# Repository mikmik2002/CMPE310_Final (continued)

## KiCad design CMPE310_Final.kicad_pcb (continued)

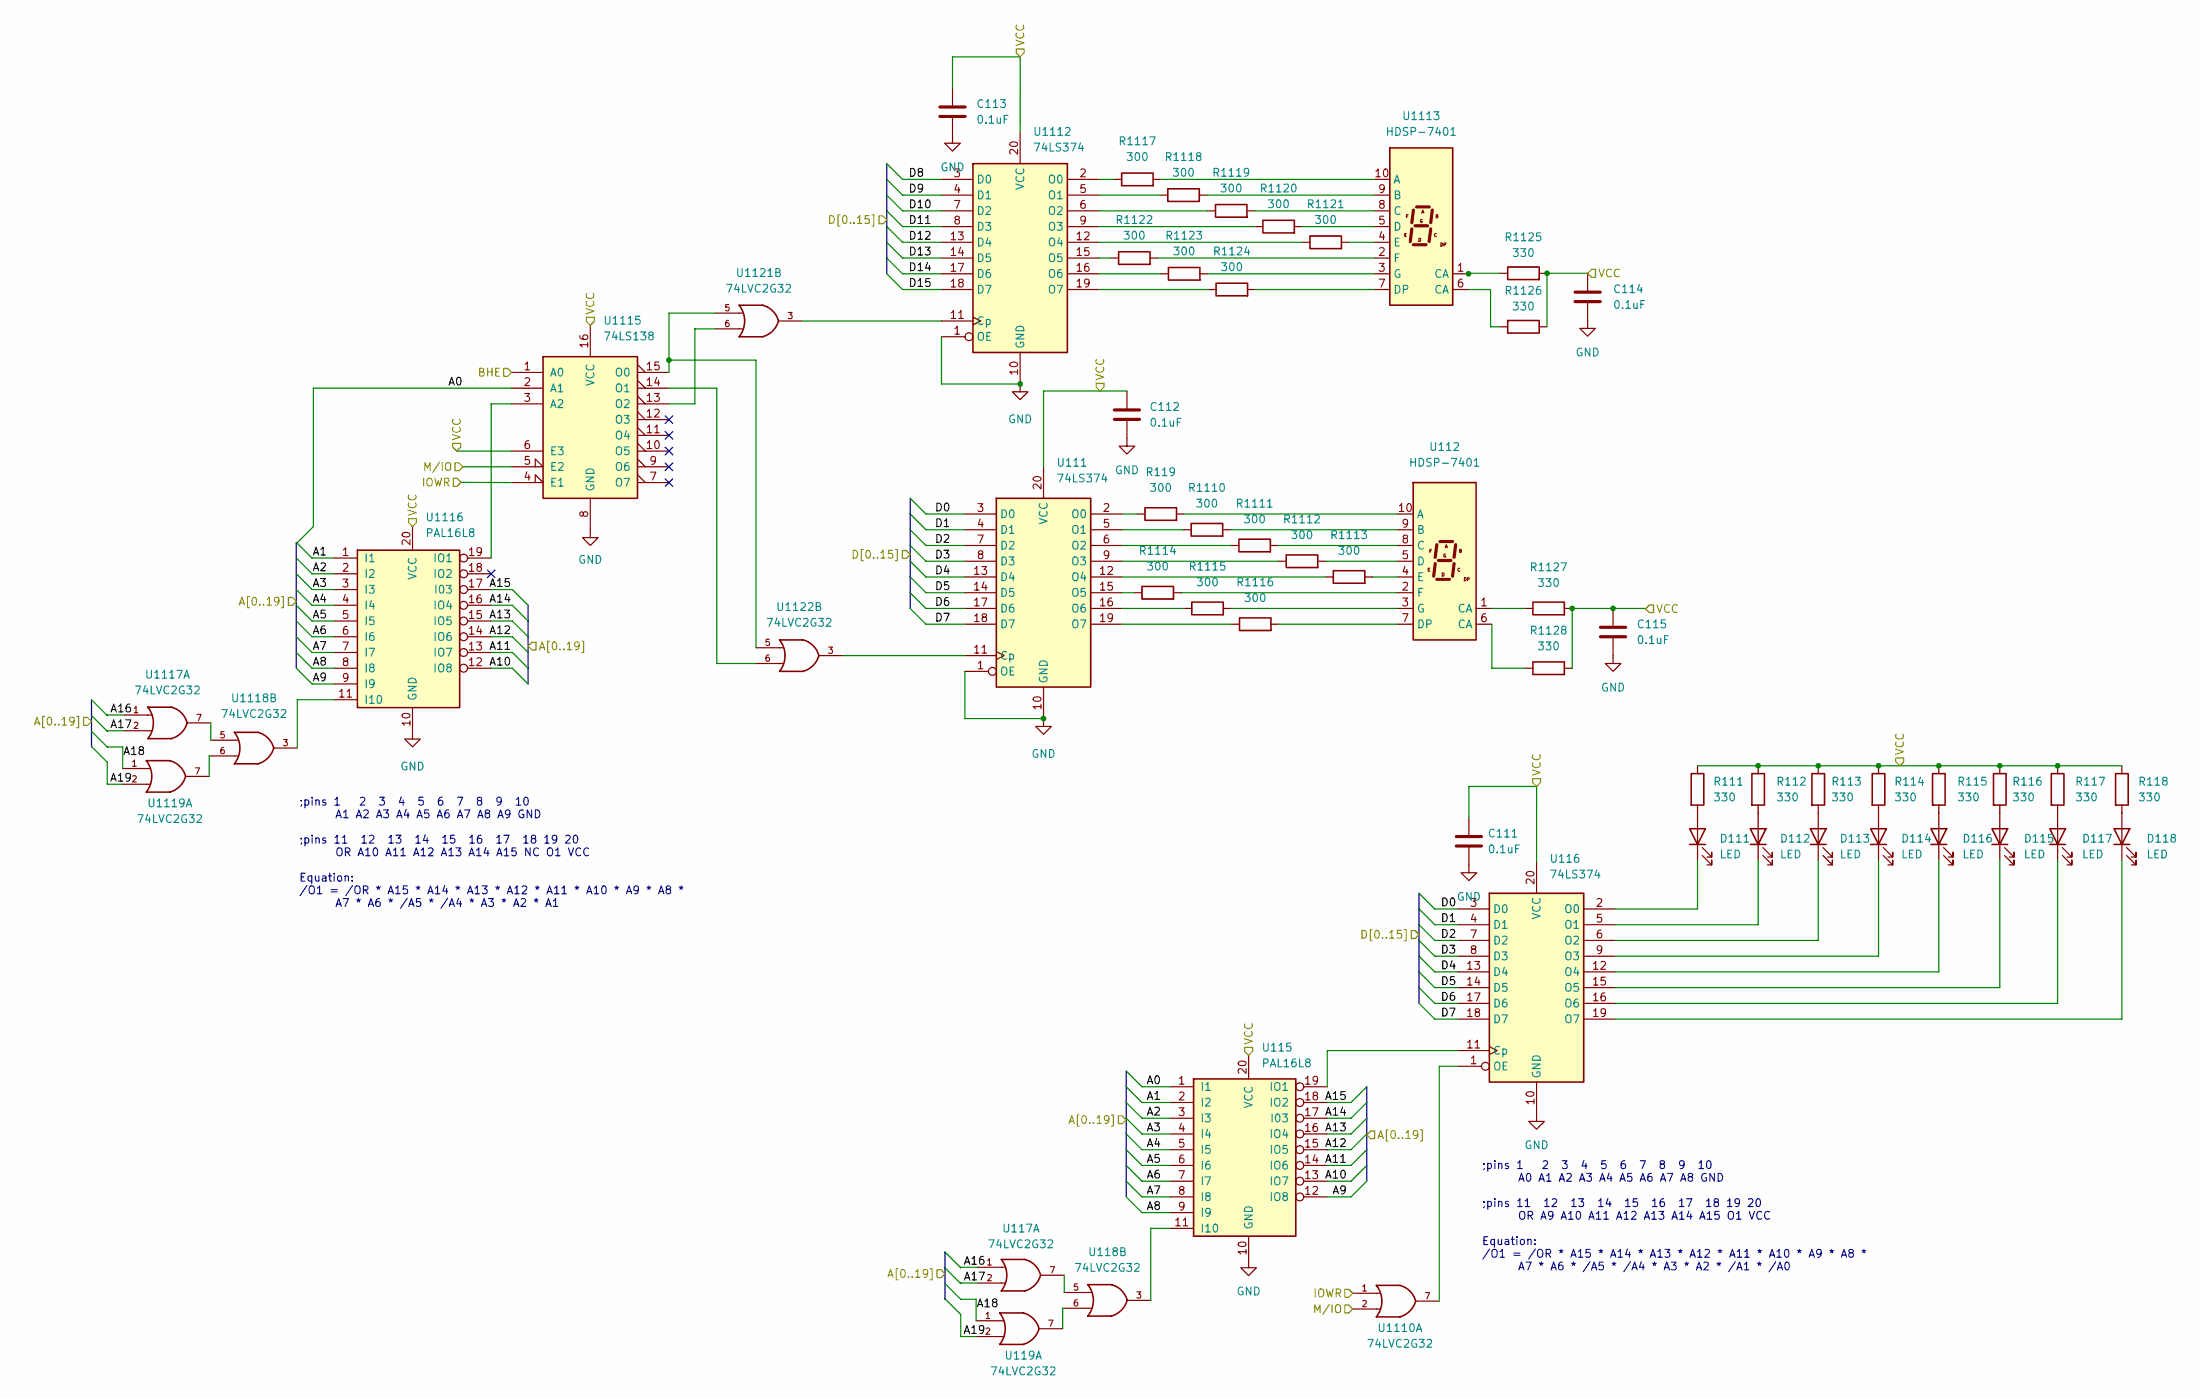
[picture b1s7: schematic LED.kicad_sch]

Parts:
C111, C112, C113, C114, C115: 0.1uF; C_Axial_L3.8mm_D2.6mm_P7.50mm_Horizontal
D111, D112, D113, D114, D115, D116, D117, D118: LED; LED_D1.8mm_W1.8mm_H2.4mm_Horizontal_O1.27mm_Z1.6mm
R111, R112, R113, R114, R115, R116, R117, R118, R1125, R1126, R1127, R1128: 330; R_Axial_DIN0204_L3.6mm_D1.6mm_P1.90mm_Vertical
R119, R1110, R1111, R1112, R1113, R1114, R1115, R1116, R1117, R1118, R1119, R1120, R1121, R1122, R1123, R1124: 300; R_Axial_DIN0204_L3.6mm_D1.6mm_P1.90mm_Vertical
U111, U116, U1112: 74LS374; DIP-20_W7.62mm
U112, U1113: HDSP-7401
U115, U1116: PAL16L8; DIP-20_W7.62mm
U117, U118, U119, U1110, U1117, U1118, U1119, U1121, U1122: 74LVC2G32
U1115: 74LS138; DIP-16_W7.62mm

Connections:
A0: U115.1 (I1), U1115.2 (A1); also elsewhere on the board
A1: U115.2 (I2), U1116.1 (I1); also elsewhere on the board
A2: U115.3 (I3), U1116.2 (I2); also elsewhere on the board
A3: U115.4 (I4), U1116.3 (I3); also elsewhere on the board
A4: U115.5 (I5), U1116.4 (I4); also elsewhere on the board
A5: U115.6 (I6), U1116.5 (I5); also elsewhere on the board
A6: U115.7 (I7), U1116.6 (I6); also elsewhere on the board
A7: U115.8 (I8), U1116.7 (I7); also elsewhere on the board
A8: U115.9 (I9), U1116.8 (I8); also elsewhere on the board
A9: U115.12 (IO8), U1116.9 (I9); also elsewhere on the board
A10: U115.13 (IO7), U1116.12 (IO8); also elsewhere on the board
A11: U115.14 (IO6), U1116.13 (IO7); also elsewhere on the board
A12: U115.15 (IO5), U1116.14 (IO6); also elsewhere on the board
A13: U115.16 (IO4), U1116.15 (IO5); also elsewhere on the board
A14: U115.17 (I03), U1116.16 (IO4); also elsewhere on the board
A15: U115.18 (IO2), U1116.17 (I03); also elsewhere on the board
A16: U117.1, U1117.1; also elsewhere on the board
A17: U117.2, U1117.2; also elsewhere on the board
A18: U119.1, U1119.1; also elsewhere on the board
A19: U119.2, U1119.2; also elsewhere on the board
BHE: U1115.1 (A0); also elsewhere on the board
D0: U111.3 (D0), U116.3 (D0); also elsewhere on the board
D1: U111.4 (D1), U116.4 (D1); also elsewhere on the board
D2: U111.7 (D2), U116.7 (D2); also elsewhere on the board
D3: U111.8 (D3), U116.8 (D3); also elsewhere on the board
D4: U111.13 (D4), U116.13 (D4); also elsewhere on the board
D5: U111.14 (D5), U116.14 (D5); also elsewhere on the board
D6: U111.17 (D6), U116.17 (D6); also elsewhere on the board
D7: U111.18 (D7), U116.18 (D7); also elsewhere on the board
D8: U1112.3 (D0); also elsewhere on the board
D9: U1112.4 (D1); also elsewhere on the board
D10: U1112.7 (D2); also elsewhere on the board
D11: U1112.8 (D3); also elsewhere on the board
D12: U1112.13 (D4); also elsewhere on the board
D13: U1112.14 (D5); also elsewhere on the board
D14: U1112.17 (D6); also elsewhere on the board
D15: U1112.18 (D7); also elsewhere on the board
GND: C111.2, C112.2, C113.2, C114.2, C115.2, U111.1 (OE), U111.10 (GND), U115.10 (GND), U116.10 (GND), U117.4 (GND), U118.4 (GND), U119.4 (GND), U1110.4 (GND), U1112.1 (OE), U1112.10 (GND), U1115.8 (GND), U1116.10 (GND), U1117.4 (GND), U1118.4 (GND), U1119.4 (GND), U1121.4 (GND), U1122.4 (GND); also elsewhere on the board
M/IO: U1110.2, U1115.5 (E2); also elsewhere on the board
unnamed: D111.1 (K), U116.2 (O0)
unnamed: D111.2 (A), R111.2
unnamed: D112.1 (K), U116.5 (O1)
unnamed: D112.2 (A), R112.2
unnamed: D113.1 (K), U116.6 (O2)
unnamed: D113.2 (A), R113.2
unnamed: D114.1 (K), U116.9 (O3)
unnamed: D114.2 (A), R114.2
unnamed: D115.1 (K), U116.15 (O5)
unnamed: D115.2 (A), R116.2
unnamed: D116.1 (K), U116.12 (O4)
unnamed: D116.2 (A), R115.2
unnamed: D117.1 (K), U116.16 (O6)
unnamed: D117.2 (A), R117.2
unnamed: D118.1 (K), U116.19 (O7)
unnamed: D118.2 (A), R118.2
unnamed: R119.1, U111.2 (O0)
unnamed: R119.2, U112.10 (A)
unnamed: R1110.1, U111.5 (O1)
unnamed: R1110.2, U112.9 (B)
unnamed: R1111.1, U111.6 (O2)
unnamed: R1111.2, U112.8 (C)
unnamed: R1112.1, U111.9 (O3)
unnamed: R1112.2, U112.5 (D)
unnamed: R1113.1, U111.12 (O4)
unnamed: R1113.2, U112.4 (E)
unnamed: R1114.1, U111.15 (O5)
unnamed: R1114.2, U112.2 (F)
unnamed: R1115.1, U111.16 (O6)
unnamed: R1115.2, U112.3 (G)
unnamed: R1116.1, U111.19 (O7)
unnamed: R1116.2, U112.7 (DP)
unnamed: R1117.1, U1112.2 (O0)
unnamed: R1117.2, U1113.10 (A)
unnamed: R1118.1, U1112.5 (O1)
unnamed: R1118.2, U1113.9 (B)
unnamed: R1119.1, U1112.6 (O2)
unnamed: R1119.2, U1113.8 (C)
unnamed: R1120.1, U1112.9 (O3)
unnamed: R1120.2, U1113.5 (D)
unnamed: R1121.1, U1112.12 (O4)
unnamed: R1121.2, U1113.4 (E)
unnamed: R1122.1, U1112.15 (O5)
unnamed: R1122.2, U1113.2 (F)
unnamed: R1123.1, U1112.16 (O6)
unnamed: R1123.2, U1113.3 (G)
unnamed: R1124.1, U1112.19 (O7)
unnamed: R1124.2, U1113.7 (DP)
unnamed: R1125.1, U1113.1 (CA)
unnamed: R1126.2, U1113.6 (CA)
unnamed: R1127.1, U112.1 (CA)
unnamed: R1128.1, U112.6 (CA)
unnamed: U111.11 (Cp), U1122.3
unnamed: U115.11 (I10), U118.3
unnamed: U115.19 (IO1), U116.11 (Cp)
unnamed: U117.7, U118.5
unnamed: U118.6, U119.7
unnamed: U116.1 (OE), U1110.7
unnamed: U1112.11 (Cp), U1121.3
unnamed: U1115.3 (A2), U1116.19 (IO1)
unnamed: U1115.13 (O2), U1121.6
unnamed: U1115.14 (O1), U1122.6
unnamed: U1115.15 (O0), U1121.5, U1122.5
unnamed: U1116.11 (I10), U1118.3
unnamed: U1117.7, U1118.5
unnamed: U1118.6, U1119.7
VCC: C111.1, C112.1, C113.1, C114.1, C115.1, R111.1, R112.1, R113.1, R114.1, R115.1, R116.1, R117.1, R118.1, R1125.2, R1126.1, R1127.2, R1128.2, U111.20 (VCC), U115.20 (VCC), U116.20 (VCC), U117.8 (VCC), U118.8 (VCC), U119.8 (VCC), U1110.8 (VCC), U1112.20 (VCC), U1115.6 (E3), U1115.16 (VCC), U1116.20 (VCC), U1117.8 (VCC), U1118.8 (VCC), U1119.8 (VCC), U1121.8 (VCC), U1122.8 (VCC); also elsewhere on the board
WR: U1110.1, U1115.4 (E1); also elsewhere on the board

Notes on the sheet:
;pins 1 2 3 4 5 6 7 8 9 10 A0 A1 A2 A3 A4 A5 A6 A7 A8 GND ;pins 11 12 13 14 15 16 17 18 19 20 OR A9 A10 A11 A12 A13 A14 A15 O1 VCC Equation: /O1 = /OR * A15 * A14 * A13 * A12 * A11 * A10 * A9 * A8 * A7 * A6 * /A5 * /A4 * A3 * A2 * /A1 * /A0
;pins 1 2 3 4 5 6 7 8 9 10 A1 A2 A3 A4 A5 A6 A7 A8 A9 GND ;pins 11 12 13 14 15 16 17 18 19 20 OR A10 A11 A12 A13 A14 A15 NC O1 VCC Equation: /O1 = /OR * A15 * A14 * A13 * A12 * A11 * A10 * A9 * A8 * A7 * A6 * /A5 * /A4 * A3 * A2 * A1

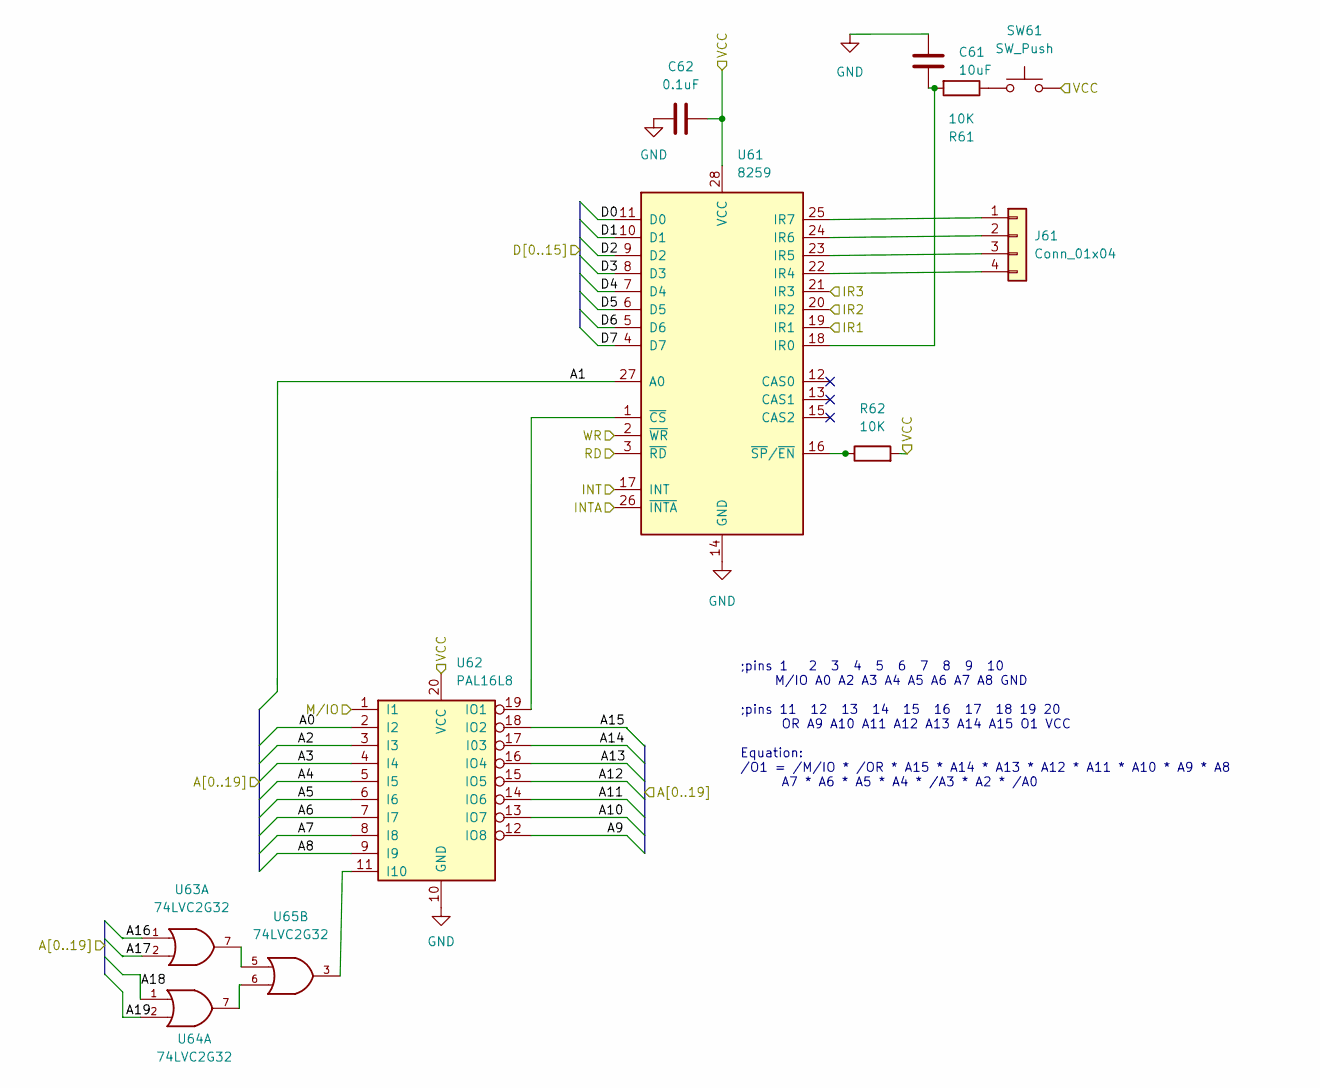
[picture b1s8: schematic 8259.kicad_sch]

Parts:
C61: 10uF; C_Axial_L3.8mm_D2.6mm_P7.50mm_Horizontal
C62: 0.1uF; C_Axial_L3.8mm_D2.6mm_P7.50mm_Horizontal
J61: Conn_01x04; PinHeader_1x04_P1.00mm_Vertical
R61, R62: 10K; R_Axial_DIN0204_L3.6mm_D1.6mm_P1.90mm_Vertical
SW61: SW_Push; SW_Tactile_Straight_KSA0Axx1LFTR
U61: 8259; DIP-28_W15.24mm
U62: PAL16L8; DIP-20_W7.62mm
U63, U64, U65: 74LVC2G32

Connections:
/8259 Bullet 6/IR2: U61.20 (IR2); also elsewhere on the board
A0: U62.2 (I2); also elsewhere on the board
A1: U61.27 (A0); also elsewhere on the board
A2: U62.3 (I3); also elsewhere on the board
A3: U62.4 (I4); also elsewhere on the board
A4: U62.5 (I5); also elsewhere on the board
A5: U62.6 (I6); also elsewhere on the board
A6: U62.7 (I7); also elsewhere on the board
A7: U62.8 (I8); also elsewhere on the board
A8: U62.9 (I9); also elsewhere on the board
A9: U62.12 (IO8); also elsewhere on the board
A10: U62.13 (IO7); also elsewhere on the board
A11: U62.14 (IO6); also elsewhere on the board
A12: U62.15 (IO5); also elsewhere on the board
A13: U62.16 (IO4); also elsewhere on the board
A14: U62.17 (I03); also elsewhere on the board
A15: U62.18 (IO2); also elsewhere on the board
A16: U63.1; also elsewhere on the board
A17: U63.2; also elsewhere on the board
A18: U64.1; also elsewhere on the board
A19: U64.2; also elsewhere on the board
D0: U61.11 (D0); also elsewhere on the board
D1: U61.10 (D1); also elsewhere on the board
D2: U61.9 (D2); also elsewhere on the board
D3: U61.8 (D3); also elsewhere on the board
D4: U61.7 (D4); also elsewhere on the board
D5: U61.6 (D5); also elsewhere on the board
D6: U61.5 (D6); also elsewhere on the board
D7: U61.4 (D7); also elsewhere on the board
GND: C61.2, C62.1, U61.14 (GND), U62.10 (GND), U63.4 (GND), U64.4 (GND), U65.4 (GND); also elsewhere on the board
INTA: U61.26 (~INTA); also elsewhere on the board
INTR: U61.17 (INT); also elsewhere on the board
IR1: U61.19 (IR1); also elsewhere on the board
IR3: U61.21 (IR3); also elsewhere on the board
M/IO: U62.1 (I1); also elsewhere on the board
unnamed: C61.1, R61.2, U61.18 (IR0)
unnamed: J61.1, U61.25 (IR7)
unnamed: J61.2, U61.24 (IR6)
unnamed: J61.3, U61.23 (IR5)
unnamed: J61.4, U61.22 (IR4)
unnamed: R61.1, SW61.1
unnamed: R62.1, U61.16 (~SP/~EN)
unnamed: U61.1 (~CS), U62.19 (IO1)
unnamed: U62.11 (I10), U65.3
unnamed: U63.7, U65.5
unnamed: U64.7, U65.6
RD: U61.3 (~RD); also elsewhere on the board
VCC: C62.2, R62.2, SW61.2, U61.28 (VCC), U62.20 (VCC), U63.8 (VCC), U64.8 (VCC), U65.8 (VCC); also elsewhere on the board
WR: U61.2 (~WR); also elsewhere on the board

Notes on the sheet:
;pins 1 2 3 4 5 6 7 8 9 10 M/IO A0 A2 A3 A4 A5 A6 A7 A8 GND ;pins 11 12 13 14 15 16 17 18 19 20 OR A9 A10 A11 A12 A13 A14 A15 O1 VCC Equation: /O1 = /M/IO * /OR * A15 * A14 * A13 * A12 * A11 * A10 * A9 * A8 A7 * A6 * A5 * A4 * /A3 * A2 * /A0

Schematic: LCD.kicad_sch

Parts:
DS101: LCD4x20; Mouser Part Number 763-0420AZFLYBW33V3
U102: PAL16L8; DIP-20_W7.62mm
U103, U104, U105: 74LVC2G32

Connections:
/LCD Bullet 10/CS: DS101.6 (E), U102.19 (IO1)
A0: U102.1 (I1); also elsewhere on the board
A1: DS101.4 (RS); also elsewhere on the board
A2: U102.2 (I2); also elsewhere on the board
A3: U102.3 (I3); also elsewhere on the board
A4: U102.4 (I4); also elsewhere on the board
A5: U102.5 (I5); also elsewhere on the board
A6: U102.6 (I6); also elsewhere on the board
A7: U102.7 (I7); also elsewhere on the board
A8: U102.8 (I8); also elsewhere on the board
A9: U102.9 (I9); also elsewhere on the board
A10: U102.12 (IO8); also elsewhere on the board
A11: U102.13 (IO7); also elsewhere on the board
A12: U102.14 (IO6); also elsewhere on the board
A13: U102.15 (IO5); also elsewhere on the board
A14: U102.16 (IO4); also elsewhere on the board
A15: U102.17 (I03); also elsewhere on the board
A16: U103.1; also elsewhere on the board
A17: U103.2; also elsewhere on the board
A18: U104.1; also elsewhere on the board
A19: U104.2; also elsewhere on the board
D0: DS101.7 (DB0); also elsewhere on the board
D1: DS101.8 (DB1); also elsewhere on the board
D2: DS101.9 (DB2); also elsewhere on the board
D3: DS101.10 (DB3); also elsewhere on the board
D4: DS101.14 (DB7); also elsewhere on the board
D5: DS101.13 (DB6); also elsewhere on the board
D6: DS101.12 (DB5); also elsewhere on the board
D7: DS101.11 (DB4); also elsewhere on the board
GND: DS101.2 (VDD), DS101.16 (LED-), U102.10 (GND), U103.4 (GND), U104.4 (GND), U105.4 (GND); also elsewhere on the board
unnamed: U102.11 (I10), U105.3
unnamed: U103.7, U105.5
unnamed: U104.7, U105.6
VCC: DS101.1 (VSS), DS101.3 (V0), DS101.15 (LED+), U102.20 (VCC), U103.8 (VCC), U104.8 (VCC), U105.8 (VCC); also elsewhere on the board
WR: DS101.5 (R/W); also elsewhere on the board

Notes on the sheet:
;pins 1 2 3 4 5 6 7 8 9 10 A0 A2 A3 A4 A5 A6 A7 A8 A9 GND ;pins 11 12 13 14 15 16 17 18 19 20 OR A10 A11 A12 A13 A14 A15 NC O1 VCC Equation: /O1 = /OR * A15 * A14 * A13 * A12 * A11 * A10 * A9 * A8 * A7 * A6 * /A5 * A4 * /A3 * A2 * /A0

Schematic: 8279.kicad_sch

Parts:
C81: 0.1uF; C_Axial_L3.8mm_D2.6mm_P7.50mm_Horizontal
SW81, SW82, SW83, SW84, SW85, SW86, SW87, SW88, SW89, SW810, SW811, SW812, SW813, SW814, SW815, SW816, SW817, SW818, SW819, SW820, SW821, SW822: SW_Push; SW_Tactile_Straight_KSA0Axx1LFTR
U81: pkd8279
U82: PAL16L8; DIP-20_W7.62mm
U83, U84, U85: 74LVC2G32
U86: 74LS138; DIP-16_W7.62mm

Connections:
/8086 Bullet One/Reset: U81.9 (RESET); also elsewhere on the board
/8259 Bullet 6/IR2: U81.4 (IRQ); also elsewhere on the board
/8279 Bullet 8/RL0: SW83.1, SW84.1, SW85.1, SW86.1, SW87.1, U81.38 (RL0)
/8279 Bullet 8/RL1: SW88.1, SW89.1, SW810.1, SW811.1, SW812.1, U81.39 (RL1)
/8279 Bullet 8/RL2: SW813.1, SW814.1, SW815.1, SW816.1, SW817.1, U81.1 (RL2)
/8279 Bullet 8/RL3: SW818.1, SW819.1, SW820.1, SW821.1, SW822.1, U81.2 (RL3)
/8279 Bullet 8/SL0: U81.32 (SL0), U86.1 (A0)
/8279 Bullet 8/SL1: U81.33 (SL1), U86.2 (A1)
/8279 Bullet 8/SL2: U81.34 (SL2), U86.3 (A2)
A0: U82.2 (I2); also elsewhere on the board
A1: U81.21 (A0); also elsewhere on the board
A2: U82.3 (I3); also elsewhere on the board
A3: U82.4 (I4); also elsewhere on the board
A4: U82.5 (I5); also elsewhere on the board
A5: U82.6 (I6); also elsewhere on the board
A6: U82.7 (I7); also elsewhere on the board
A7: U82.8 (I8); also elsewhere on the board
A8: U82.9 (I9); also elsewhere on the board
A9: U82.12 (IO8); also elsewhere on the board
A10: U82.13 (IO7); also elsewhere on the board
A11: U82.14 (IO6); also elsewhere on the board
A12: U82.15 (IO5); also elsewhere on the board
A13: U82.16 (IO4); also elsewhere on the board
A14: U82.17 (I03); also elsewhere on the board
A15: U82.18 (IO2); also elsewhere on the board
A16: U83.1; also elsewhere on the board
A17: U83.2; also elsewhere on the board
A18: U84.1; also elsewhere on the board
A19: U84.2; also elsewhere on the board
D0: U81.12 (DB0); also elsewhere on the board
D1: U81.13 (DB1); also elsewhere on the board
D2: U81.14 (DB2); also elsewhere on the board
D3: U81.15 (DB3); also elsewhere on the board
D4: U81.16 (DB4); also elsewhere on the board
D5: U81.17 (DB5); also elsewhere on the board
D6: U81.18 (DB6); also elsewhere on the board
D7: U81.19 (DB7); also elsewhere on the board
GND: C81.1, SW81.2, SW82.2, U81.20 (VSS), U82.10 (GND), U83.4 (GND), U84.4 (GND), U85.4 (GND), U86.4 (E1), U86.5 (E2), U86.8 (GND); also elsewhere on the board
M/IO: U82.1 (I1); also elsewhere on the board
unnamed: SW81.1, U81.37 (CNTL/STB)
unnamed: SW82.1, U81.36 (SHIFT)
unnamed: SW85.2, SW810.2, SW815.2, SW820.2, U86.13 (O2)
unnamed: SW86.2, SW811.2, SW816.2, SW821.2, U86.12 (O3)
unnamed: SW87.2, SW812.2, SW817.2, SW822.2, U86.11 (O4)
unnamed: SW83.2, SW88.2, SW813.2, SW818.2, U86.15 (O0)
unnamed: SW84.2, SW89.2, SW814.2, SW819.2, U86.14 (O1)
unnamed: U81.22 (~CS), U82.19 (IO1)
unnamed: U82.11 (I10), U85.3
unnamed: U83.7, U85.5
unnamed: U84.7, U85.6
PCLK: U81.3 (CLK); also elsewhere on the board
RD: U81.10 (~RD); also elsewhere on the board
VCC: C81.2, U81.5 (RL4), U81.6 (RL5), U81.7 (RL6), U81.8 (RL7), U81.40 (VCC), U82.20 (VCC), U83.8 (VCC), U84.8 (VCC), U85.8 (VCC), U86.6 (E3), U86.16 (VCC); also elsewhere on the board
WR: U81.11 (~WR); also elsewhere on the board

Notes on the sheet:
;pins 1 2 3 4 5 6 7 8 9 10 M/IO A0 A2 A3 A4 A5 A6 A7 A8 GND ;pins 11 12 13 14 15 16 17 18 19 20 OR A9 A10 A11 A12 A13 A14 A15 O1 VCC Equation: /O1 = /M/IO * /OR * A15 * A14 * A13 * A12 * A11 * A10 * A9 * A8 A7 * A6 * A5 * A4 * /A3 * /A2 * /A0

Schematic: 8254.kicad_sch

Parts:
C71: 0.1uF; C_Axial_L3.8mm_D2.6mm_P7.50mm_Horizontal
J71, J73: Conn_01x03; PinHeader_1x03_P1.00mm_Vertical
J72: Conn_01x02; PinHeader_1x02_P1.00mm_Vertical
U71: 8254; DIP-24_W15.24mm
U72: PAL16L8; DIP-20_W7.62mm
U73: 74LVC1G332

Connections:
A0: U72.2 (I2); also elsewhere on the board
A1: U71.19 (A0); also elsewhere on the board
A2: U71.20 (A1); also elsewhere on the board
A3: U72.3 (I3); also elsewhere on the board
A4: U72.4 (I4); also elsewhere on the board
A5: U72.5 (I5); also elsewhere on the board
A6: U72.6 (I6); also elsewhere on the board
A7: U72.7 (I7); also elsewhere on the board
A8: U72.8 (I8); also elsewhere on the board
A9: U72.9 (I9); also elsewhere on the board
A10: U72.12 (IO8); also elsewhere on the board
A11: U72.13 (IO7); also elsewhere on the board
A12: U72.14 (IO6); also elsewhere on the board
A13: U72.15 (IO5); also elsewhere on the board
A14: U72.16 (IO4); also elsewhere on the board
A15: U72.17 (I03); also elsewhere on the board
A16: U72.18 (IO2); also elsewhere on the board
A17: U73.6; also elsewhere on the board
A18: U73.1; also elsewhere on the board
A19: U73.3; also elsewhere on the board
D0: U71.8 (D0); also elsewhere on the board
D1: U71.7 (D1); also elsewhere on the board
D2: U71.6 (D2); also elsewhere on the board
D3: U71.5 (D3); also elsewhere on the board
D4: U71.4 (D4); also elsewhere on the board
D5: U71.3 (D5); also elsewhere on the board
D6: U71.2 (D6); also elsewhere on the board
D7: U71.1 (D7); also elsewhere on the board
GND: C71.1, U71.12 (GND), U72.10 (GND), U73.2 (GND); also elsewhere on the board
IR1: U71.13 (OUT1); also elsewhere on the board
M/IO: U72.1 (I1); also elsewhere on the board
unnamed: J71.1, U71.9 (CLK0)
unnamed: J71.2, U71.11 (G0)
unnamed: J71.3, U71.10 (OUT0)
unnamed: J72.1, U71.15 (CLK1)
unnamed: J72.2, U71.14 (G1)
unnamed: J73.1, U71.18 (CLK2)
unnamed: J73.2, U71.16 (G2)
unnamed: J73.3, U71.17 (OUT2)
unnamed: U71.21 (~CS), U72.19 (IO1)
unnamed: U72.11 (I10), U73.4
RD: U71.22 (~RD); also elsewhere on the board
VCC: C71.2, U71.24 (VCC), U72.20 (VCC), U73.5 (VCC); also elsewhere on the board
WR: U71.23 (~WR); also elsewhere on the board

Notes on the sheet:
;pins 1 2 3 4 5 6 7 8 9 10 M/IO A2 A3 A4 A5 A6 A7 A8 OR GND ;pins 11 12 13 14 15 16 17 18 19 20 A9 A10 A11 A12 A13 A14 A15 A16 O1 VCC Equation: /O1 = /M/IO * /OR * /A16 * A15 * A14 * A13 * A12 * A11 * A10 * A9 * A8 * A7 * A6 * /A5 * A4 * A3 * /A0

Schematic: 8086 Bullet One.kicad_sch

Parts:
C11: 10uF; C_Axial_L3.8mm_D2.6mm_P7.50mm_Horizontal
C12: 0.1uF; C_Axial_L3.8mm_D2.6mm_P7.50mm_Horizontal
J1: Conn_01x20; PinHeader_1x20_P1.00mm_Vertical
J2: Conn_01x16; PinHeader_1x16_P1.00mm_Vertical
J3: Conn_01x03; PinHeader_1x03_P1.00mm_Vertical
R11: 10K; R_Axial_DIN0204_L3.6mm_D1.6mm_P1.90mm_Vertical
SW0: SW_Push; SW_Tactile_Straight_KSA0Axx1LFTR
U1: 8086_Min_Mode; DIP-40_W15.24mm
U2, U3, U4: 74AHC373; DIP-20_W7.62mm
U5, U6: 74LS245; DIP-20_W7.62mm
U7: 74LS244; DIP-20_W7.62mm

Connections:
/8086 Bullet One/AD0: U1.16 (AD0), U2.3 (D0), U5.2 (A0)
/8086 Bullet One/AD1: U1.15 (AD1), U2.4 (D1), U5.3 (A1)
/8086 Bullet One/AD2: U1.14 (AD2), U2.7 (D2), U5.4 (A2)
/8086 Bullet One/AD3: U1.13 (AD3), U2.8 (D3), U5.5 (A3)
/8086 Bullet One/AD4: U1.12 (AD4), U2.13 (D4), U5.6 (A4)
/8086 Bullet One/AD5: U1.11 (AD5), U2.14 (D5), U5.7 (A5)
/8086 Bullet One/AD6: U1.10 (AD6), U2.17 (D6), U5.8 (A6)
/8086 Bullet One/AD7: U1.9 (AD7), U2.18 (D7), U5.9 (A7)
/8086 Bullet One/AD8: U1.8 (AD8), U3.3 (D0), U6.2 (A0)
/8086 Bullet One/AD9: U1.7 (AD9), U3.4 (D1), U6.3 (A1)
/8086 Bullet One/AD10: U1.6 (AD10), U3.7 (D2), U6.4 (A2)
/8086 Bullet One/AD11: U1.5 (AD11), U3.8 (D3), U6.5 (A3)
/8086 Bullet One/AD12: U1.4 (AD12), U3.13 (D4), U6.6 (A4)
/8086 Bullet One/AD13: U1.3 (AD13), U3.14 (D5), U6.7 (A5)
/8086 Bullet One/AD14: U1.2 (AD14), U3.17 (D6), U6.8 (A6)
/8086 Bullet One/AD15: U1.39 (AD15), U3.18 (D7), U6.9 (A7)
/8086 Bullet One/AD16: U1.38 (A16/S3), U4.4 (D1)
/8086 Bullet One/AD17: U1.37 (A17/S4), U4.7 (D2)
/8086 Bullet One/AD18: U1.36 (A18/S5), U4.8 (D3)
/8086 Bullet One/AD19: U1.35 (A19/S6), U4.13 (D4)
/8086 Bullet One/Clk: U1.19 (CLK); also elsewhere on the board
/8086 Bullet One/READY: U1.22 (READY); also elsewhere on the board
/8086 Bullet One/Reset: U1.21 (RESET); also elsewhere on the board
A0: J1.1, U2.2 (O0); also elsewhere on the board
A1: J1.2, U2.5 (O1); also elsewhere on the board
A2: J1.3, U2.6 (O2); also elsewhere on the board
A3: J1.4, U2.9 (O3); also elsewhere on the board
A4: J1.5, U2.12 (O4); also elsewhere on the board
A5: J1.6, U2.15 (O5); also elsewhere on the board
A6: J1.7, U2.16 (O6); also elsewhere on the board
A7: J1.8, U2.19 (O7); also elsewhere on the board
A8: J1.9, U3.2 (O0); also elsewhere on the board
A9: J1.10, U3.5 (O1); also elsewhere on the board
A10: J1.11, U3.6 (O2); also elsewhere on the board
A11: J1.12, U3.9 (O3); also elsewhere on the board
A12: J1.13, U3.12 (O4); also elsewhere on the board
A13: J1.14, U3.15 (O5); also elsewhere on the board
A14: J1.15, U3.16 (O6); also elsewhere on the board
A15: J1.16, U3.19 (O7); also elsewhere on the board
A16: J1.17, U4.5 (O1); also elsewhere on the board
A17: J1.18, U4.6 (O2); also elsewhere on the board
A18: J1.19, U4.9 (O3); also elsewhere on the board
A19: J1.20, U4.12 (O4); also elsewhere on the board
BHE: U4.2 (O0); also elsewhere on the board
D0: J2.1, U5.18 (B0); also elsewhere on the board
D1: J2.2, U5.17 (B1); also elsewhere on the board
D2: J2.3, U5.16 (B2); also elsewhere on the board
D3: J2.4, U5.15 (B3); also elsewhere on the board
D4: J2.5, U5.14 (B4); also elsewhere on the board
D5: J2.6, U5.13 (B5); also elsewhere on the board
D6: J2.7, U5.12 (B6); also elsewhere on the board
D7: J2.8, U5.11 (B7); also elsewhere on the board
D8: J2.9, U6.18 (B0); also elsewhere on the board
D9: J2.10, U6.17 (B1); also elsewhere on the board
D10: J2.11, U6.16 (B2); also elsewhere on the board
D11: J2.12, U6.15 (B3); also elsewhere on the board
D12: J2.13, U6.14 (B4); also elsewhere on the board
D13: J2.14, U6.13 (B5); also elsewhere on the board
D14: J2.15, U6.12 (B6); also elsewhere on the board
D15: J2.16, U6.11 (B7); also elsewhere on the board
GND: C11.2, C12.1, U1.1 (GND), U1.20 (GND), U1.31 (HOLD), U2.1 (OE), U2.10 (GND), U3.1 (OE), U3.10 (GND), U4.1 (OE), U4.10 (GND), U5.10 (GND), U6.10 (GND), U7.1 (OEa), U7.8 (I3a), U7.10 (GND), U7.11 (I0b), U7.13 (I1b), U7.15 (I2b), U7.17 (I3b), U7.19 (OEb); also elsewhere on the board
INTA: U1.24 (~INTA); also elsewhere on the board
INTR: U1.18 (INTR); also elsewhere on the board
M/IO: J3.1, U7.18 (O0a); also elsewhere on the board
unnamed: C11.1, R11.2, U1.17 (NMI)
unnamed: R11.1, SW0.2
unnamed: U1.25 (ALE), U2.11 (LE), U3.11 (LE), U4.11 (LE)
unnamed: U1.26 (~DEN), U5.19 (CE), U6.19 (CE)
unnamed: U1.27 (DT/~R), U5.1 (A->B), U6.1 (A->B)
unnamed: U1.28 (M/~IO), U7.2 (I0a)
unnamed: U1.29 (~WR), U7.4 (I1a)
unnamed: U1.32 (~RD), U7.6 (I2a)
unnamed: U1.34 (~BHE/S7), U4.3 (D0)
RD: J3.3, U7.14 (O2a); also elsewhere on the board
VCC: C12.2, SW0.1, U1.23 (~TEST), U1.33 (MN/~MX), U1.40 (VCC), U2.20 (VCC), U3.20 (VCC), U4.20 (VCC), U5.20 (VCC), U6.20 (VCC), U7.20 (VCC); also elsewhere on the board
WR: J3.2, U7.16 (O1a); also elsewhere on the board

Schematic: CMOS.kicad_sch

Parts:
C21, C22: 0.1uF; C_Axial_L3.8mm_D2.6mm_P7.50mm_Horizontal
U21, U22: 28F010
U23, U24: 74LS138; DIP-16_W7.62mm

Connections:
A0: U24.5 (E2); also elsewhere on the board
A1: U21.12 (A0), U22.12 (A0); also elsewhere on the board
A2: U21.11 (A1), U22.11 (A1); also elsewhere on the board
A3: U21.10 (A2), U22.10 (A2); also elsewhere on the board
A4: U21.9 (A3), U22.9 (A3); also elsewhere on the board
A5: U21.8 (A4), U22.8 (A4); also elsewhere on the board
A6: U21.7 (A5), U22.7 (A5); also elsewhere on the board
A7: U21.6 (A6), U22.6 (A6); also elsewhere on the board
A8: U21.5 (A7), U22.5 (A7); also elsewhere on the board
A9: U21.27 (A8), U22.27 (A8); also elsewhere on the board
A10: U21.26 (A9), U22.26 (A9); also elsewhere on the board
A11: U21.23 (A10), U22.23 (A10); also elsewhere on the board
A12: U21.25 (A11), U22.25 (A11); also elsewhere on the board
A13: U21.4 (A12), U22.4 (A12); also elsewhere on the board
A14: U21.28 (A13), U22.28 (A13); also elsewhere on the board
A15: U21.29 (A14), U22.29 (A14); also elsewhere on the board
A16: U21.3 (A15), U22.3 (A15); also elsewhere on the board
A17: U21.2 (A16), U22.2 (A16); also elsewhere on the board
A18: U23.1 (A0), U24.1 (A0); also elsewhere on the board
A19: U23.2 (A1), U24.2 (A1); also elsewhere on the board
BHE: U23.5 (E2); also elsewhere on the board
D0: U22.13 (DQ0); also elsewhere on the board
D1: U22.14 (DQ1); also elsewhere on the board
D2: U22.15 (DQ2); also elsewhere on the board
D3: U22.17 (DQ3); also elsewhere on the board
D4: U22.18 (DQ4); also elsewhere on the board
D5: U22.19 (DQ5); also elsewhere on the board
D6: U22.20 (DQ6); also elsewhere on the board
D7: U22.21 (DQ7); also elsewhere on the board
D8: U21.13 (DQ0); also elsewhere on the board
D9: U21.14 (DQ1); also elsewhere on the board
D10: U21.15 (DQ2); also elsewhere on the board
D11: U21.17 (DQ3); also elsewhere on the board
D12: U21.18 (DQ4); also elsewhere on the board
D13: U21.19 (DQ5); also elsewhere on the board
D14: U21.20 (DQ6); also elsewhere on the board
D15: U21.21 (DQ7); also elsewhere on the board
GND: C21.1, C22.1, U21.1 (VPP), U21.16 (VSS), U22.1 (VPP), U22.16 (VSS), U23.3 (A2), U23.4 (E1), U23.8 (GND), U24.3 (A2), U24.4 (E1), U24.8 (GND); also elsewhere on the board
M/IO: U23.6 (E3), U24.6 (E3); also elsewhere on the board
unnamed: U21.22 (CE), U23.12 (O3)
unnamed: U22.22 (CE), U24.7 (O7)
RD: U21.24 (OE), U22.24 (OE); also elsewhere on the board
VCC: C21.2, C22.2, U21.32 (VCC), U22.32 (VCC), U23.16 (VCC), U24.16 (VCC); also elsewhere on the board
WR: U21.31 (WE), U22.31 (WE); also elsewhere on the board

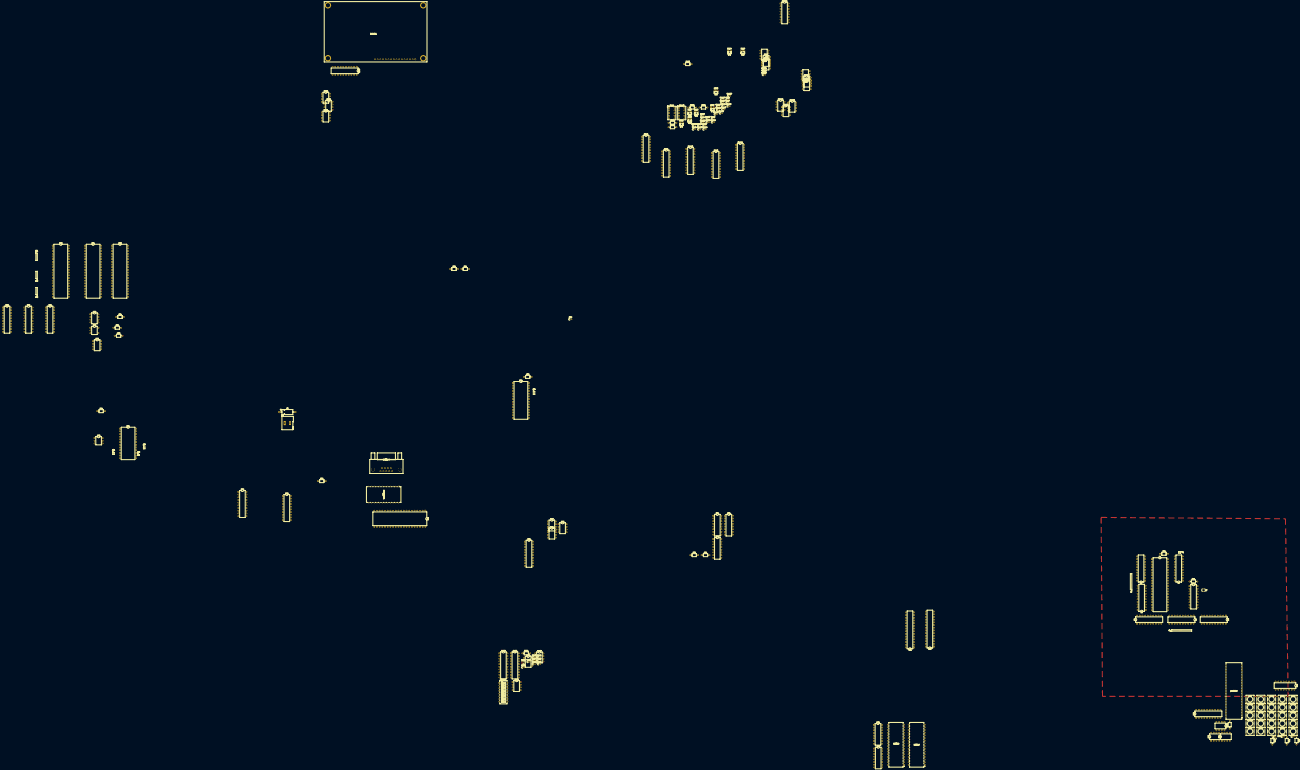
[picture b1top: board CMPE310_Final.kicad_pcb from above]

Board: 6 copper layers, 181 parts (0 on the bottom side), 254 nets.

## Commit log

2022-05-05 Added KiCad Files one resistor
2022-05-05 Added Second Resistor
2022-05-05 Added stuff
2022-05-06 finished bullet 6
2022-05-06 Added bullet 6
2022-05-06 stuff
2022-05-09 finished design
2022-05-11 Finished
